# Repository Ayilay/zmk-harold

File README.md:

# Harold Keyboard

A fully-split fully-wireless keyboard that I made for myself. Powered by ZMK, a 750mAh LiPo, and an Seeeduino XIAO NRF52840.

## Repository Files

`config` has the zmk config files.
`hardware/ergogen` has the [Ergogen](https://github.com/ergogen/ergogen) files that were used to generate PCB Layout.
`hardware/pcb` has the KiCAD PCB files.

## Pictures

This is my favorite use case: Comfy Coding

This is what it looks like under the hood:

## FAQ

#### WOA That's so cool! You should sell these!
No. I made this keyboard to fill a very particular need.
This keyboard was highly customized for myself. There are plenty of other companies out there
with exceptional split wireless keyboards.

#### Doesn't the battery run out?
Many wireless keyboards I've seen use a dinky 250 mAh LiPo battery, because it's very small.
Luckily I was able to squeeze a 750 mAh battery into mine, and I can go up to a month without charging it.

#### It must have such high typing latency, it's Bluetooth!
Nope! The latency is so negligible that it may as well be wired. I can easily exceed 100WPM with no
discernible lag.

#### But you can't use it for gaming.
Wrong. I game with it all the time. I'm not a leet-pro-mlg gamer, I just game casually now and then.
Games like Team Fortress 2 and Portal, nothing crazy. Works perfectly fine.

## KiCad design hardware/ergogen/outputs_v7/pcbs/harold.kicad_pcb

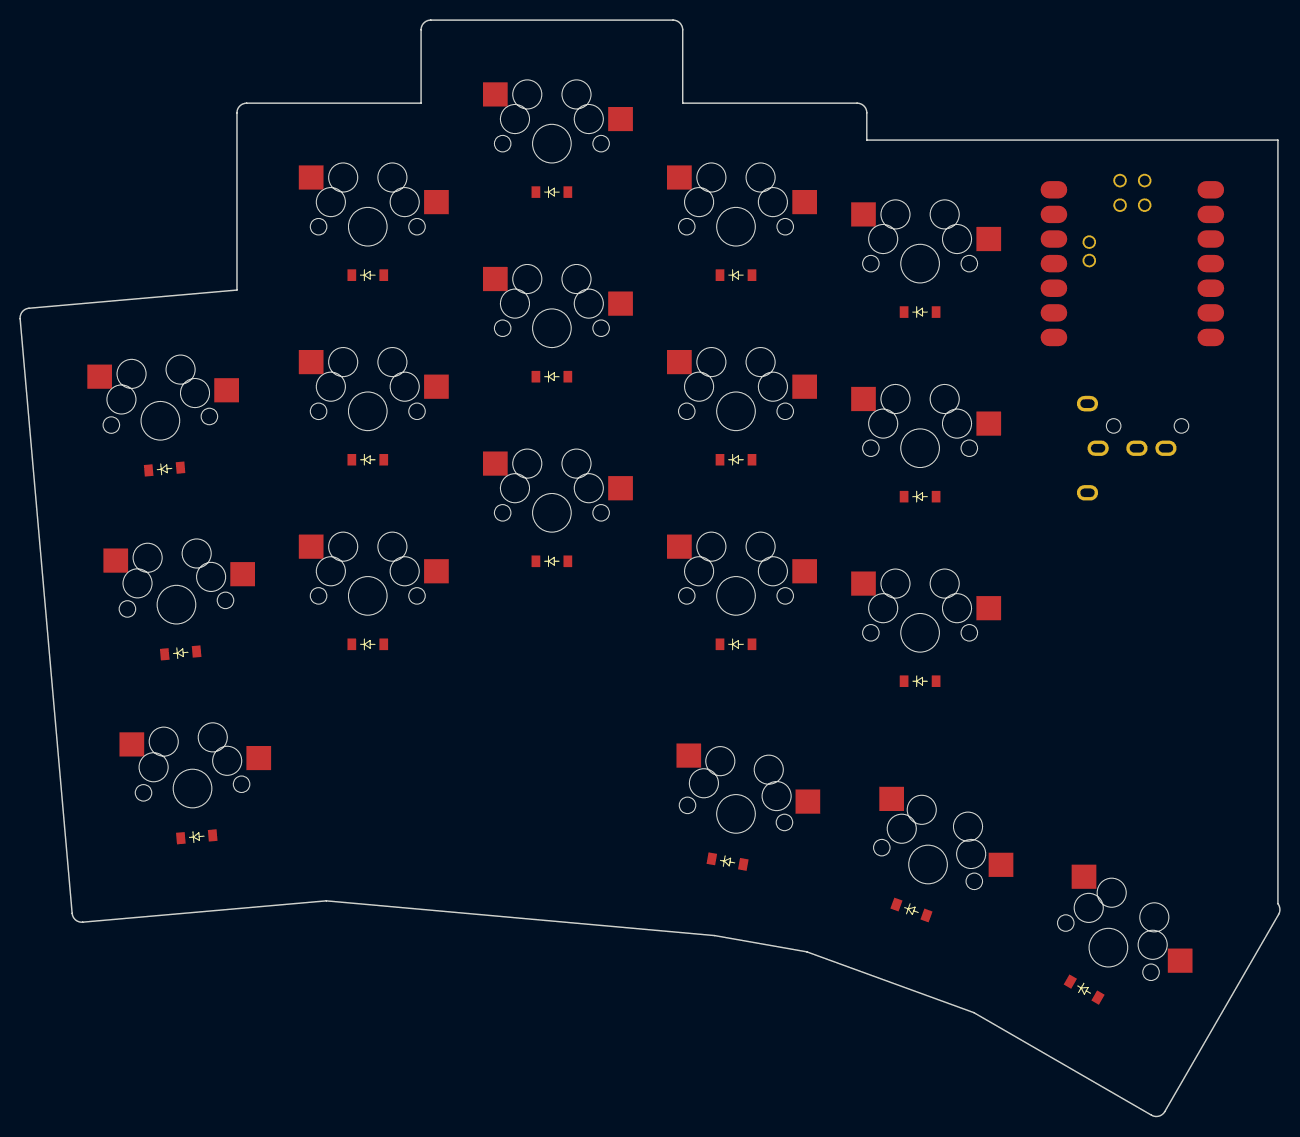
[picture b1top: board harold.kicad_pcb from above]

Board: 2 copper layers, 130.0 x 113.2 mm, 38 parts (0 on the bottom side), 29 nets, no tracks yet.

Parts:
D1, D2, D3, D4, D5, D6, D7, D8, D9, D10, D11, D12, D13, D14, D15, D16, D17, D18: ComboDiode
MCU1: XiaoBLE_SMD
S1, S2, S3, S4, S5, S6, S7, S8, S9, S10, S11, S12, S13, S14, S15, S16, S17, S18: MX
TRRS1: TRRS-PJ-320A-dual

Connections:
COL_Indx: MCU1.4, S10.2, S11.2, S12.2, S17.2
COL_Innr: MCU1.5, S13.2, S14.2, S15.2, S18.2
COL_Midd: MCU1.3, S7.2, S8.2, S9.2, S16.2
COL_Pink: MCU1.1, S1.2, S2.2, S3.2
COL_Ring: MCU1.2, S4.2, S5.2, S6.2
GND: MCU1.13, MCU1.18, TRRS1.2, TRRS1.3
ROW_Bot: D1.1, D4.1, D7.1, D10.1, D13.1, MCU1.6
ROW_Home: D2.1, D5.1, D8.1, D11.1, D14.1, MCU1.8
ROW_Thumb: D16.1, D17.1, D18.1
ROW_Top: D3.1, D6.1, D9.1, D12.1, D15.1, MCU1.9, TRRS1.1
homey_thumb_row: D17.2, S17.1
index_bottom: D10.2, S10.1
index_home: D11.2, S11.1
index_top: D12.2, S12.1
inner_bottom: D13.2, S13.1
inner_home: D14.2, S14.1
inner_top: D15.2, S15.1
middle_bottom: D7.2, S7.1
middle_home: D8.2, S8.1
middle_top: D9.2, S9.1
pinky_bottom: D1.2, S1.1
pinky_home: D2.2, S2.1
pinky_top: D3.2, S3.1
reachy_thumb_row: D18.2, S18.1
ring_bottom: D4.2, S4.1
ring_home: D5.2, S5.1
ring_top: D6.2, S6.1
test1: MCU1.10, TRRS1.4
tucky_thumb_row: D16.2, S16.1

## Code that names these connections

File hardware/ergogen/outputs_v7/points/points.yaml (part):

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                    shift:
                        - 0
                        - -5
        colnet: COL_Pink
        rownet: ROW_Bot
        name: matrix_pinky_bottom
        colrow: pinky_bottom
        col: &ref_0
            rotate: 5
            key:
                colnet: COL_Pink
            stagger: 0
            spread: 0
            origin:
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                    shift:
                        - 0
                        - -5
        colnet: COL_Pink
        rownet: ROW_Home
        name: matrix_pinky_home
        colrow: pinky_home
        col: *ref_0
        row: home
matrix_pinky_top:
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                    shift:
                        - 0
                        - -5
        colnet: COL_Pink
        rownet: ROW_Top
        name: matrix_pinky_top
        colrow: pinky_top
        col: *ref_0
        row: top
matrix_ring_bottom:
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
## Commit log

2023-01-14 Initial User Config.
2023-01-16 Created Harold shield, here goes
2023-01-17 Keymap and Matrix Transform changes
2023-01-17 Fix keymap bug, add majority of Ayilay Atreus layout
2023-01-17 Fix KP capitalization bug
2023-01-17 Fix plus bug??
2023-01-17 replace sym layer w/ default for test
2023-01-17 typo in vol down
2023-01-17 re-add symbol layer
2023-01-17 remove plus key with A
2023-01-17 what the hell
2023-01-17 left-half fix
2023-01-17 found the stupid ampersand typo
2023-01-17 Add enter and tab keys to thumb cluster
2023-01-17 Change thumb keys from none to transparent
2023-01-17 Layout changes
    - Add zero
    - Add deep-sleep for 1 minute, TODO change it back asap
2023-01-17 Swap 0 and Backspace because it was awkward.
    Fix deep sleep timing back to 15 minutes
2023-01-17 Swap Tab and Enter bc for the life of me I wont get used to this
2023-01-17 Add TriLayer (Config) with some neatos
    - Microcontroller Reset (pinkie top-row, both halves)
    - Bootloader mode (pinkie home-row, both halves)
    - Alt-F4 (Application Quit) on index top-row
2023-01-27 Added automaitc build script it's cool
2023-01-27 Added settings-reset build directive
2023-02-05 Main is f**ked, backport it here and fix everything
2023-02-06 Add quit shortcut but it doesn't work
2023-02-07 Increase mod-tap delay slightly for homerow mods
2023-02-09 Fix Alt-F4 not working
2023-02-09 Add tapdance for TMUX and CapsWord
2023-02-22 Fix annoying windows HRM, and add Gaming Layer 1
2023-03-06 tuned HRM win key better for lang switching
2023-03-06 add 10 empty layer placeholders
2023-03-21 increased idle sleep timeout to 30 mins
2023-05-15 Made compile script more resilient to non-existent directories
2023-05-16 Significantly improved gaming layer + super layer, it works awesome!
2023-05-20 A few keymap + config changes
    - Add Space to right-half of GM1 layer
    - Remove RESET key from config layer, it was useless
    - Clean build-script slightly
2023-05-30 Move Win/Super key from home row to Z/? keys because it keeps triggering
2023-06-09 Add F-Key layer
2024-08-25 Game layer changes + Build script enhance
2024-08-25 Move tilde key to homerow pinky
2024-08-25 Remove unused shield files
2024-10-08 Add readme and pictures
2024-10-09 add FAQ
2024-12-25 Add debounce (hardware is slowly becoming worse...)
